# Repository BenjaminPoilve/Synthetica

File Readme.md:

# Synthetica

**Read about this project [here](https://www.benjaminpoilve.com/projects/synthetica.html)**

The basic idea is to create a simple instrument, with on one side the chord selection, and on the other side the note selection (within that chord). 

I will use a teensy as main board for a few reason:

* Teensy are awesome
* Teensy audio library is awesome

Will be major only, minor by transposition as with the harmonica. Choice of chords, look [here](https://www.hooktheory.com/blog/i-analyzed-the-chords-of-1300-popular-songs-for-patterns-this-is-what-i-found/)

## BOM

The teensy 3.2 will do:

* I2S output (Pin 9,11,22,23)
* I2C to touch chip (Pin 18, 19)
* 5 setting potentiometer (Pin 14, 16, 17 ,20)
* 3 switch for fondamental select (Pin 2, 3, 4)
* 1 calibrate switch (Pin 5)
* 1 select switch (automatically go from jack to USB) (Pin 6)

#### Summing Up

| Part Name  |  Value | Reference document | Count |   
|---|---|---|---|
|  Teensy 3.2  | None  | [:link:](https://www.mouser.fr/ProductDetail/Adafruit/2756?qs=sGAEpiMZZMuSK2mCDyT9crBR9UUNDPltQqpZaqADC8g%3d)   | 1  |   
| Potentiometer |  100K  | [:link:](https://www.mouser.fr/ProductDetail/Bourns/PTV09A-4020U-B104?qs=%2fha2pyFaduhvapXs4is1IL5MTuddxsTCkr0fc6JrD7g2QA59By%252bflw%3d%3d)  | 5  |  
| 3 DIP switch | None  | [:link:](https://www.mouser.fr/ProductDetail/CK/SDA03H1BD?qs=%2fha2pyFadujO%252bD1d0%2fA%252bWLFkqEV%2fBrm6lAVSO35a%2fyM%3d)  | 1  |  
| DP3T switch | None  | [:link:](https://www.mouser.fr/ProductDetail/CK/OS203012MU5QP1?qs=%2fha2pyFaduixNo%252bc4UFQdwKaLaiPJgx8VDniAIBXV%2fi9XId9YW60xA%3d%3d)  | 1  |  
|CS4344| None  | [:link:](https://www.mouser.fr/ProductDetail/Cirrus-Logic/CS4344-CZZ?qs=sGAEpiMZZMuYaq4aOfOV%252bEKBckiASbBM)  | 1  |  
| QT2120 | None  | [:link:](https://www.mouser.fr/ProductDetail/Microchip-Technology-Atmel/AT42QT2120-XUR?qs=sGAEpiMZZMsVh0scArXy39GoFU3Q6EzjtRsYSCRuHwE%3d)  | 1  | 
|KMR2 switch | None  | [:link:](https://www.mouser.fr/ProductDetail/CK/KMR231NGLFS?qs=sGAEpiMZZMsgGjVA3toVBPoYbSFtFlEEZ%2foF5FrvAI8%3d)  | 1  | 
|AAA Holder | None  | [:link:](https://www.mouser.fr/ProductDetail/Keystone-Electronics/82?qs=sGAEpiMZZMsQtlBhqKq43YbiTvCk46ni)  | 6  | 
| Jack Connector | None | [:link:](https://www.mouser.fr/ProductDetail/Switchcraft/35RAPC4BHN2?qs=sGAEpiMZZMv0W4pxf2HiV3fTUvSc3cBd2jSbOSYtPwc%3d) | 1|
| Capacitor | 0.1uf | [:link:](https://www.mouser.fr/ProductDetail/KEMET/C1206C104MMREC7210?qs=sGAEpiMZZMsh%252b1woXyUXj6NiChfwzFayyr7622zgSs8%3d) | 2|
| Polarised capacitor | 1uf | [:link:](https://www.mouser.fr/ProductDetail/AVX/F971E105MAAHT3?qs=sGAEpiMZZMukHu%252bjC5l7Yco8kKEM9uRbb54cngRv8Go%3d) | 1|
| Polarised capacitor | 3.3uf | [:link:](https://www.mouser.fr/ProductDetail/AVX/F971C335MAAHT3?qs=sGAEpiMZZMukHu%252bjC5l7Yco8kKEM9uRb9xft%252bS%252bywL0%3d) | 3|
| Polarised capacitor | 10uf | [:link:](https://www.mouser.fr/ProductDetail/KEMET/T491A106K016AT7280?qs=sGAEpiMZZMukHu%252bjC5l7YfojpQgWN8ePgdsBtgcMwmI%3d) | 1|
| Diode | None | [:link:](https://www.mouser.fr/ProductDetail/ROHM-Semiconductor/RB160MM-40TFTR?qs=sGAEpiMZZMtQ8nqTKtFS%2fE7Jc%252bkgrGbhyaeUfQeErNAgcMoCDuX0KA%3d%3d) | 1|
| Resistor | 470 | [:link:](https://www.mouser.fr/ProductDetail/KOA-Speer/SG73G2BTTD4700D?qs=sGAEpiMZZMukHu%252bjC5l7YW4TDpT9cCWZ7Y3pXreM%2fjU%3d) | 2|
| Resistor | 2k2 | [:link:](https://www.mouser.fr/ProductDetail/TE-Connectivity-Holsworthy/CRGP1206F2K2?qs=sGAEpiMZZMve4%2fbfQkoj%252bNpsGoFOGLriQenFA4%2f97jM%3d) | 2|
| Resistor | 10k | [:link:](https://www.mouser.fr/ProductDetail/Yageo/AC1206FR-1010KL?qs=sGAEpiMZZMve4%2fbfQkoj%252bO7jQjGJ2PPFatQsu75yNqQ%3d) | 13|

## Issues, and feedbacks

#### From First PCB

* Get longer pad traces for chips. This version is reflow friendly, but hard to hand solder
* The interruptor is backward, issue with trace
* The voltage drop of the diode is too high! Wrong part? Had to bypass it.
* Pots are too big. Should change version
* Should use two AAA, use a voltage converter
* Should put component more to the center to make the side more easy to cover
* Issue with jack trace, does not go through PCB hole.
* See if there is feeback on the sensors.
* Should really try to avoid vias on capacitive lines. At least put them closer to the center

#### Other

* Issue with [USB](https://forum.pjrc.com/threads/54239-USB-Audio-Clicking-Noise/page3?highlight=noise+audio)
* Probably needs to have a status led

## Thanks and people that helped

* Everybody that helped me on [that thread](https://forum.pjrc.com/threads/55137-I2S-output-with-CS4344) 
* @otem for its polysynth

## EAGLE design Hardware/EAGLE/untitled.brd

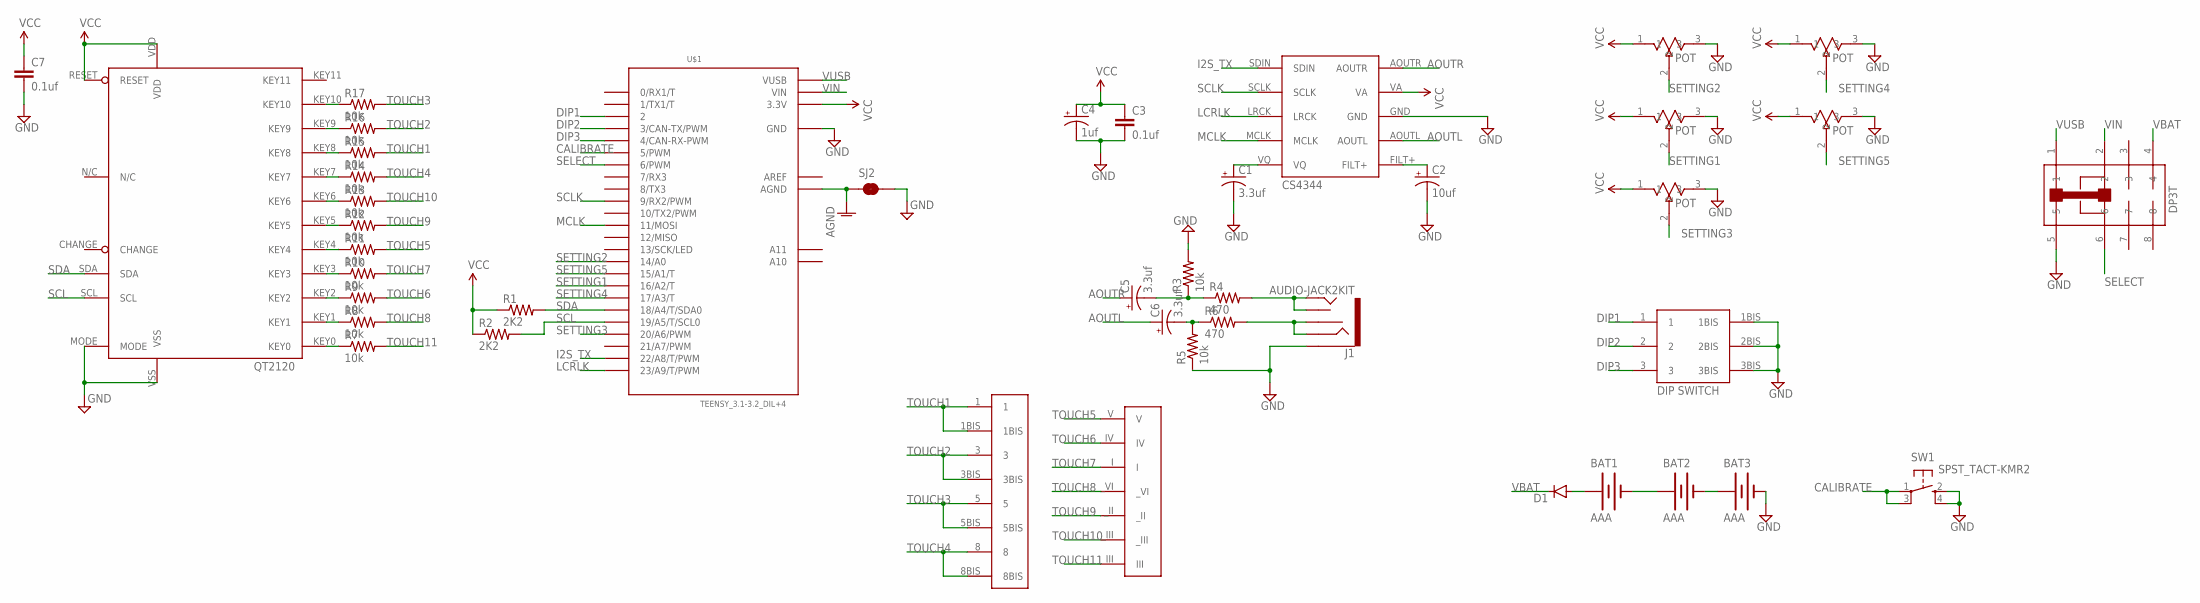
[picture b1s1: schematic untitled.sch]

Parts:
BAT1, BAT2, BAT3: AAA; BATTERY-AAA-KIT
C1, C5, C6: 3.3uf; EIA3216
C2: 10uf; EIA3216
C3, C7: 0.1uf; 1206
C4: 1uf; EIA3216
D1: DIODESOD123; SOD-123
DIP1: SDA03H1BD
DP3T1: OS203012MU5QP1
J1: AUDIO-JACK2KIT; AUDIO-JACK-KIT
POT2, POT3, POT5: PTV09A-4020U-B104
R1, R2: 2K2; 1206
R3, R5, R7, R8, R9, R10, R11, R12, R13, R14, R15, R16, R17: 10k; 1206
R4, R6: 470; 1206
SJ2: JUMPER-PAD-2-NC_BY_TRACE; PAD-JUMPER-2-NC_BY_TRACE_YES_SILK
SW1: SPST_TACT-KMR2; KMR2
SWEEP: PTV09A-4020U-B104
U1: CS4344
U$1: TEENSY_3.1-3.2_DIL+4; TEENSY_3.0-3.2&LC_DIL+4
U$2: QT2120
U$4: NOTEPAD
U$5: CHORDPAD
VOLUME: PTV09A-4020U-B104

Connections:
AGND: SJ2.1, U$1.AGND
AOUTL: C6.A (+), U1.AOUTL
AOUTR: C5.A (+), U1.AOUTR
AREF: U$1.AREF
CALIBRATE: SW1.1, SW1.3 (P1), U$1.5 (5/PWM)
DIP1: DIP1.1, U$1.2
DIP2: DIP1.2, U$1.3 (3/CAN-TX/PWM)
DIP3: DIP1.3, U$1.4 (4/CAN-RX-PWM)
GND: BAT3.GND@1 (-), C1.C (-), C2.C (-), C3.2, C4.C (-), C7.2, DIP1.1BIS, DIP1.2BIS, DIP1.3BIS, DP3T1.5, J1.SLEEVE, POT2.3, POT3.3, POT5.3, R3.2, R5.1, SJ2.2, SW1.2 (S), SW1.4 (S1), SWEEP.3, U1.GND, U$1.GND, U$2.MODE, U$2.VSS, VOLUME.3
I2S_TX: U1.SDIN, U$1.22/A8 (22/A8/T/PWM)
LCRLK: U1.LRCK, U$1.23/A9 (23/A9/T/PWM)
LEFT: J1.TIP, J1.TSH, R4.2
MCLK: U1.MCLK, U$1.11 (11/MOSI)
unnamed: BAT1.GND@1 (-), BAT2.PWR@1 (+)
unnamed: C1.A (+), U1.VQ
unnamed: BAT2.GND@1 (-), BAT3.PWR@1 (+)
unnamed: C2.A (+), U1.FILT+
unnamed: C5.C (-), R3.1, R4.1
unnamed: C6.C (-), R5.2, R6.1
unnamed: R17.1, U$2.KEY10
unnamed: R16.1, U$2.KEY9
unnamed: R15.1, U$2.KEY8
unnamed: R14.1, U$2.KEY7
unnamed: R13.1, U$2.KEY6
unnamed: R12.1, U$2.KEY5
unnamed: R11.1, U$2.KEY4
unnamed: R10.1, U$2.KEY3
unnamed: BAT1.PWR@1 (+), D1.A
unnamed: R9.1, U$2.KEY2
unnamed: R8.1, U$2.KEY1
unnamed: R7.1, U$2.KEY0
unnamed: J1.RING, J1.RSH, R6.2
SCL: R2.2, U$1.19/A5 (19/A5/T/SCL0), U$2.SCL
SCLK: U1.SCLK, U$1.9 (9/RX2/PWM)
SDA: R1.2, U$1.18/A4 (18/A4/T/SDA0), U$2.SDA
SELECT: DP3T1.6, U$1.6 (6/PWM)
SETTING1: POT2.2, U$1.16/A2 (16/A2/T)
SETTING2: U$1.14/A0, VOLUME.2
SETTING3: POT3.2, U$1.20/A6 (20/A6/PWM)
SETTING4: SWEEP.2, U$1.17/A3 (17/A3/T)
SETTING5: POT5.2, U$1.15/A1 (15/A1/T)
TOUCH1: R15.2, U$4.1, U$4.1BIS
TOUCH2: R16.2, U$4.3, U$4.3BIS
TOUCH3: R17.2, U$4.5, U$4.5BIS
TOUCH4: R14.2, U$4.8, U$4.8BIS
TOUCH5: R11.2, U$5.V
TOUCH6: R9.2, U$5.IV
TOUCH7: R10.2, U$5.I
TOUCH8: R8.2, U$5._VI
TOUCH9: R12.2, U$5._II
TOUCH10: R13.2, U$5._III
TOUCH11: R7.2, U$5.III
VBAT: D1.C, DP3T1.4
VCC: C3.1, C4.A (+), C7.1, POT2.1, POT3.1, POT5.1, R1.1, R2.1, SWEEP.1, U1.VA, U$1.3.3V, U$2.RESET, U$2.VDD, VOLUME.1
VIN: DP3T1.2, U$1.VIN
VUSB: DP3T1.1, U$1.VUSB

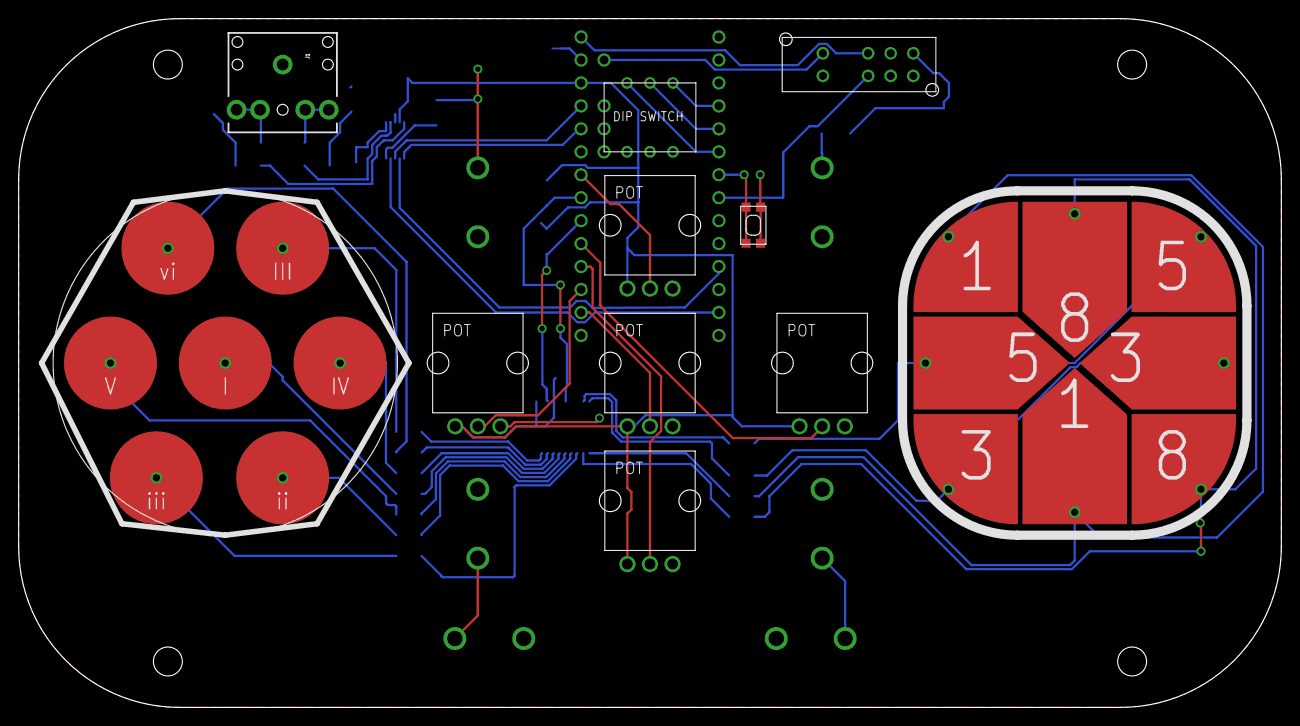
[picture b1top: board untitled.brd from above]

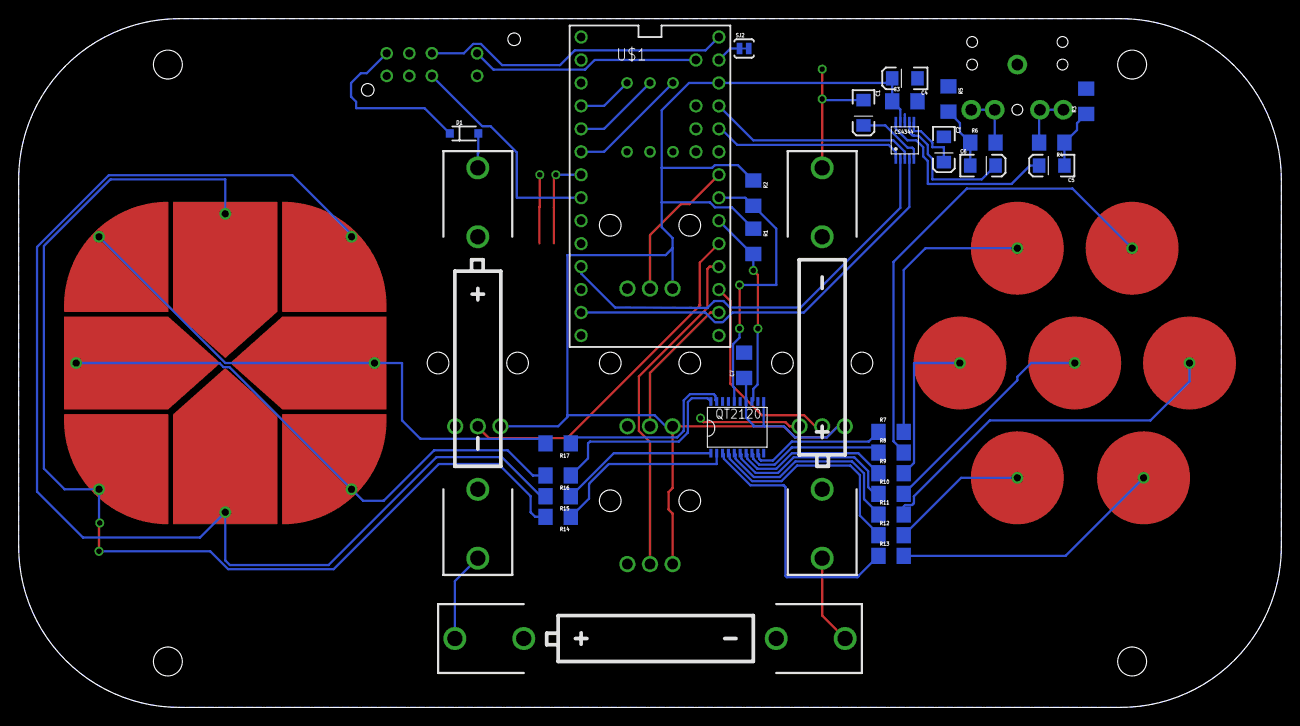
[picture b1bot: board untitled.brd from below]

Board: 2 copper layers, 139.7 x 76.2 mm, 43 parts (32 on the bottom side), 55 nets.

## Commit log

2019-02-01 Working my way on the part lists/trace
2019-02-04 V1 of board sent to fab
2019-02-11 Started assembly, updated eagles files
2019-02-11 Added more legible images
2019-02-11 modded lib for all button support
2019-02-12 After first PCB assembly, feedback and new needs
2019-02-12 Update of the capV2 lib, to have lower bounce
2019-03-23 Updated for article

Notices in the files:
parts and their libraries:
SparkFun-Electromechanical: Licensing: Creative Commons ShareAlike 4.0 International - https://creativecommons.org/licenses/by-sa/4.0
